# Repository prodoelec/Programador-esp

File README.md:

# Programador módulos ESP32 & ESP8266

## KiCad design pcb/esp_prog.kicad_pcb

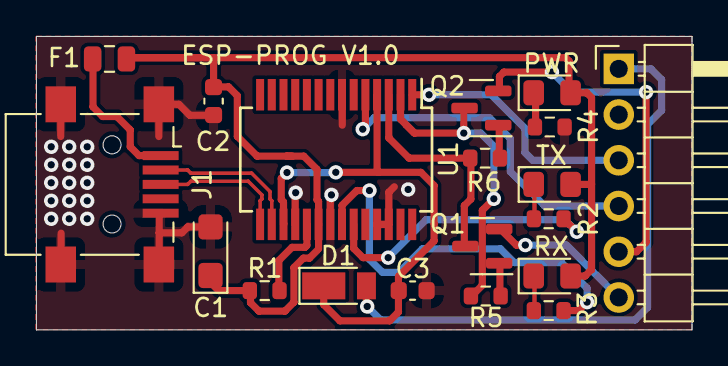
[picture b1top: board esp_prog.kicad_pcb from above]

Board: 2 copper layers, 36.4 x 16.3 mm, 19 parts (0 on the bottom side), 21 nets.

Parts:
C1: 4,7uF/6V3; CP_EIA-3216-10_Kemet-I
C2, C3: 100nF; C_0603_1608Metric
D1: SS1P3L; D_PowerDI-123
F1: 500mA; Fuse_0805_2012Metric
J1: USB_B_Mini; USB_Mini-B_Lumberg_2486_01_Horizontal
J2: ICSP; PinHeader_1x06_P2.54mm_Horizontal
L1: TX; LED_0805_2012Metric_Pad1.15x1.40mm_HandSolder
L2: RX; LED_0805_2012Metric_Pad1.15x1.40mm_HandSolder
L3: PWR; LED_0805_2012Metric_Pad1.15x1.40mm_HandSolder
Q1, Q2: BC847; SOT-23
R1, R5, R6: 10K; R_0603_1608Metric
R2, R3: 1K; R_0603_1608Metric
R4: 3K3; R_0603_1608Metric
U1: FT232RL; SSOP-28_5.3x10.2mm_P0.65mm

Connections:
+3V3: D1.2 (A), J2.1
/D+: J1.3 (D+), U1.15 (USBD+)
/D-: J1.2 (D-), U1.16 (USBD-)
CBUS0: R2.2, U1.23 (CBUS0)
CBUS1: R3.2, U1.22 (CBUS1)
DTR: Q2.3 (E), R5.2, U1.2 (DTR)
GND: C1.2, C2.2, C3.2, J1.5 (GND), J1.6 (Shield), J2.2, R4.2, U1.7 (GND), U1.18 (GND), U1.21 (GND), U1.25 (AGND), U1.26 (TEST)
GPIO0: J2.5, Q2.2 (C)
unnamed: F1.2, J1.1 (VBUS)
unnamed: L1.1 (K), R2.1
unnamed: L2.1 (K), R3.1
unnamed: L3.1 (K), R4.1
unnamed: Q1.1 (B), R5.1
unnamed: Q2.1 (B), R6.1
unnamed: C3.1, D1.1 (K), U1.4 (VCCIO), U1.17 (3V3OUT)
unnamed: R1.2, U1.19 (~RESET)
RESET: J2.6, Q1.2 (C)
RTS: Q1.3 (E), R6.2, U1.3 (RTS)
RX_PROG: J2.3, U1.1 (TXD)
TX_PROG: J2.4, U1.5 (RXD)
VBUS: C1.1, C2.1, F1.1, L1.2 (A), L2.2 (A), L3.2 (A), R1.1, U1.20 (VCC)

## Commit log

2023-02-06 original
2023-05-30 Actualizacón Readme
2023-05-30 Borrado carpeta caja
